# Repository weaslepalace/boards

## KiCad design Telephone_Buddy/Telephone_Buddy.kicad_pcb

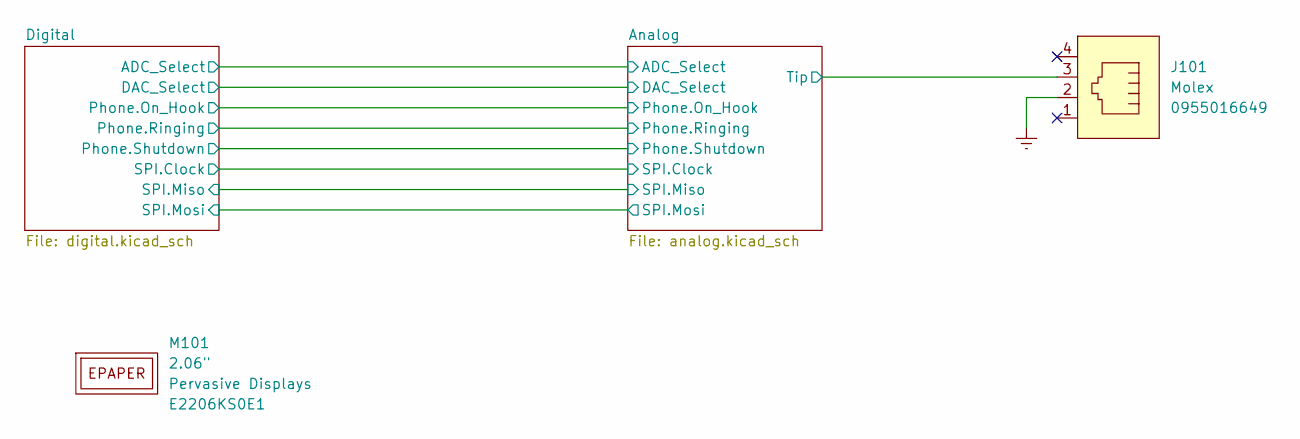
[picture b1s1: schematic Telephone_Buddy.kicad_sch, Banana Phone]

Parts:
J101: Molex_RJ11; Manufacturer Part Number 0955016649
M101: 2.06"; Pervasive_E2206KS0E1; Manufacturer Part Number E2206KS0E1

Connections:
/Analog/Tip: J101.3; also elsewhere on the board
GND: J101.2; also elsewhere on the board

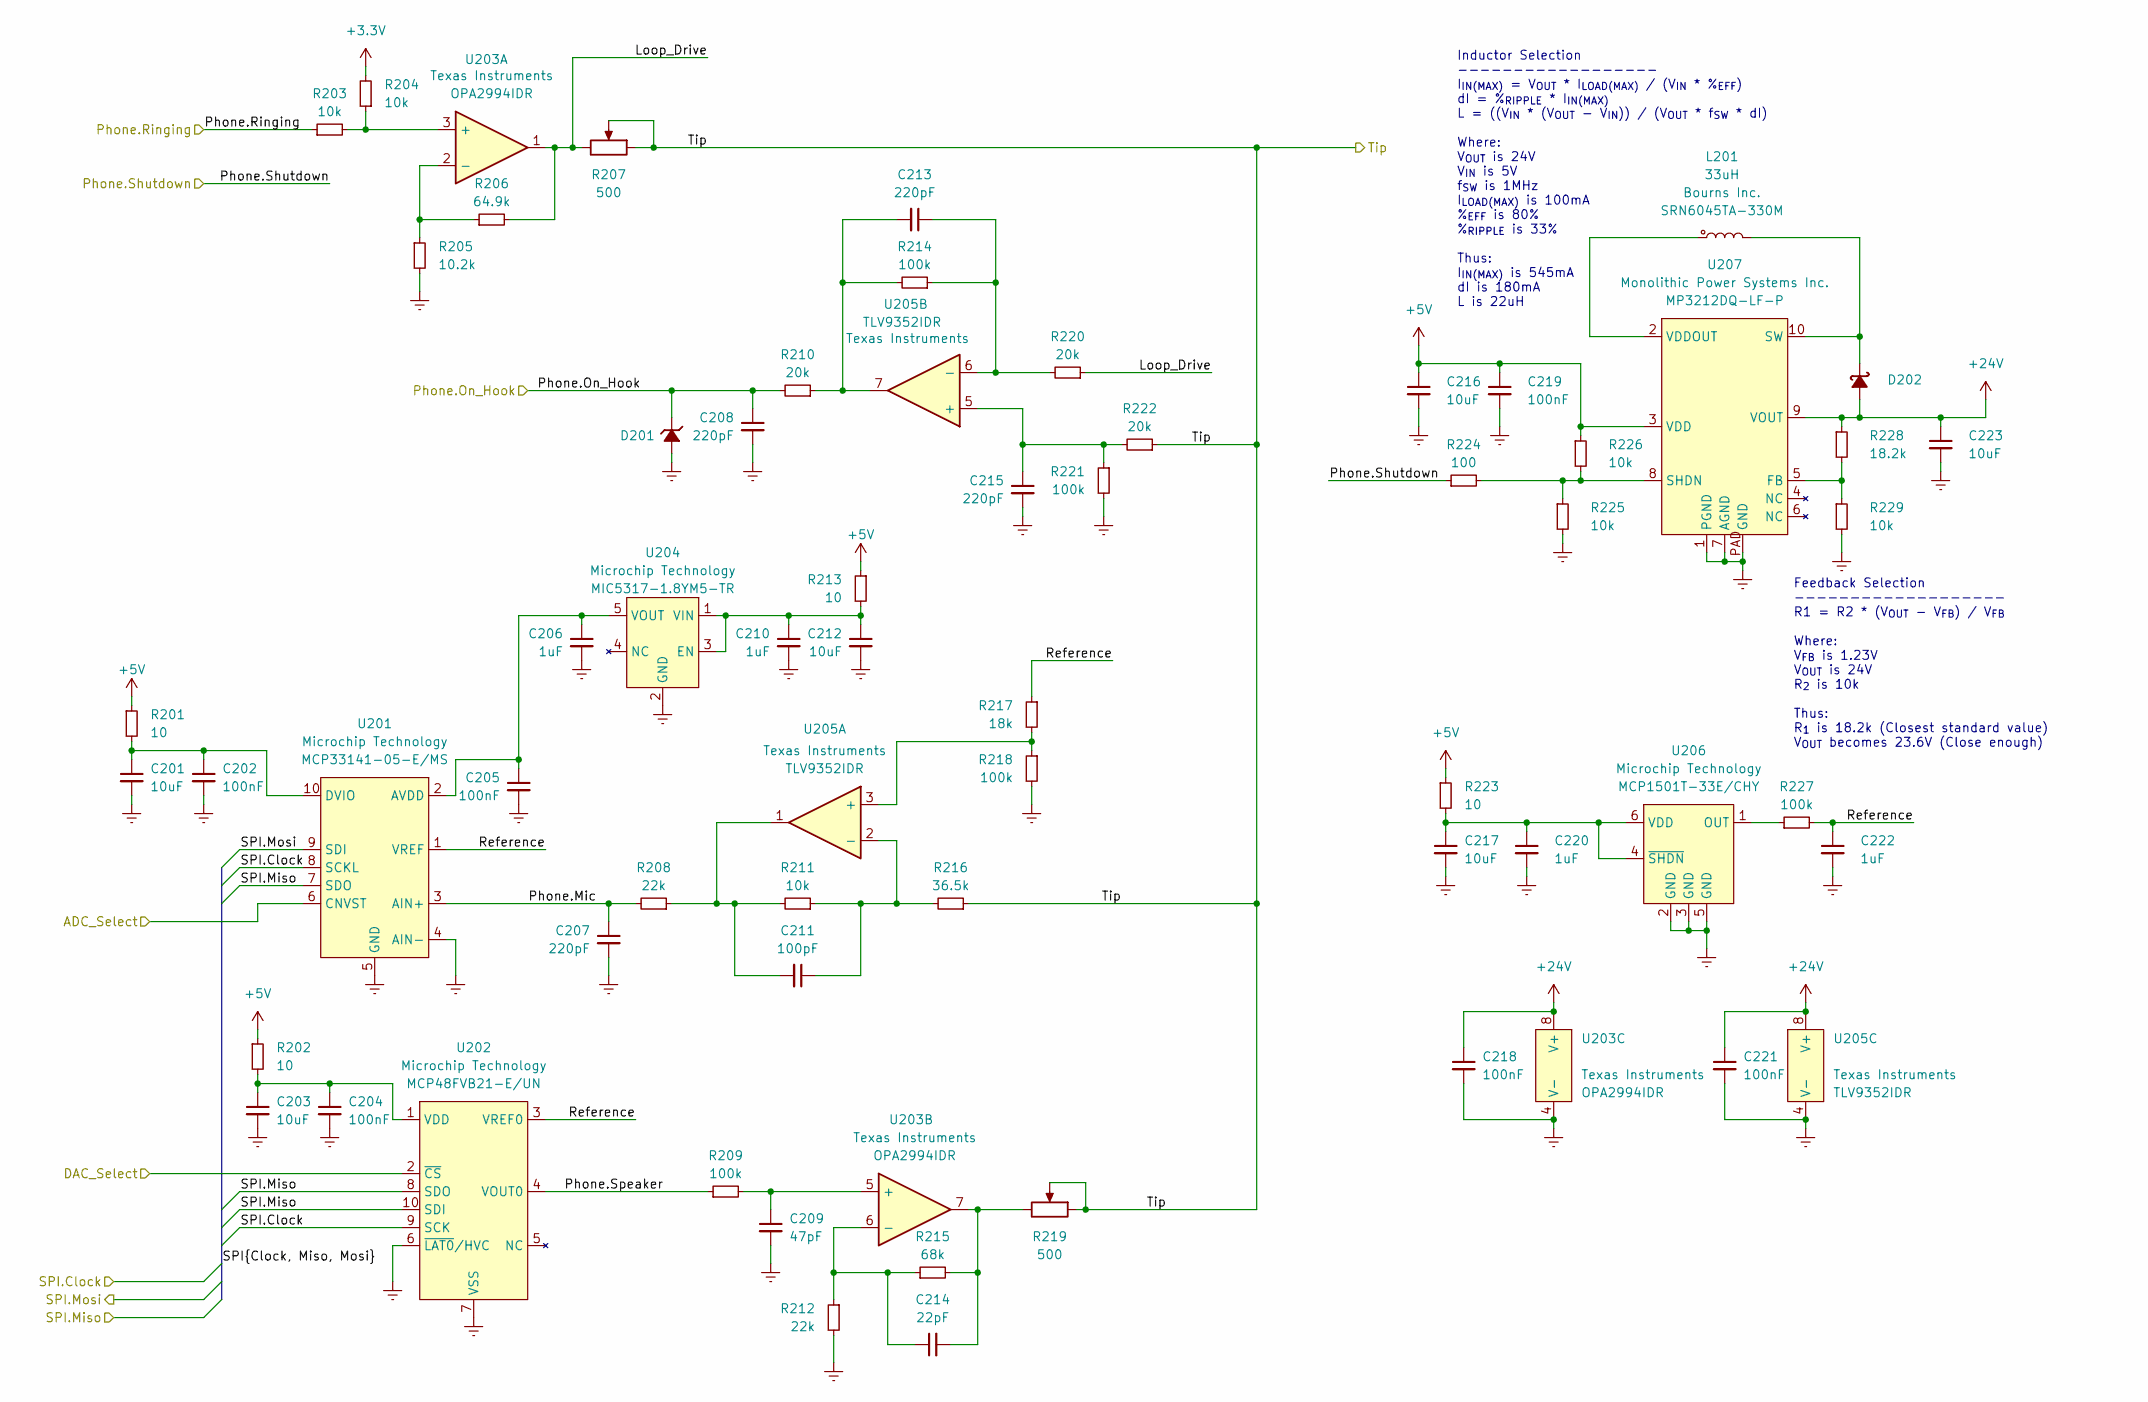
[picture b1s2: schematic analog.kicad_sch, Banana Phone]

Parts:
C201, C203, C212, C217: 10uF; C_0603; Manufacturer Part Number GRM188R61A106ME69D
C202, C204, C205, C218, C219, C221: 100nF; C_0603; Manufacturer Part Number GCJ188R72A104KA01D
C206, C210, C220, C222: 1uF; C_0603; Manufacturer Part Number GCJ188R71E105KA01D
C207, C208, C213, C215: 220pF; C_0603; Manufacturer Part Number GCM1885C2A221JA16D
C209: 47pF; C_0603; Manufacturer Part Number GCM1885C2A470JA16J
C211: 100pF; C_0603; Manufacturer Part Number GCM1885C2A101JA16D
C214: 22pF; C_0603; Manufacturer Part Number GCM1885C2A220JA16D
C216: 10uF; C_1206; Manufacturer Part Number CL31B106KAHNFNE
C223: 10uF; C_1206; Manufacturer Part Number CL31B106KBHNNNE
D201: onsemi_SOD123; Manufacturer Part Number MMSZ3V3T1G
D202: SOD-123FL; Manufacturer Part Number SS2040FL-AU_R1_000A1
L201: 33uH; Bourns_Inductor-6mmx6mm; Manufacturer Part Number SRN6045TA-330M
R201, R202, R213, R223: 10; R_0603; Manufacturer Part Number RC0603FR-0710RL
R203, R204, R211, R225, R226, R229: 10k; R_0603; Manufacturer Part Number RC0603FR-0710KL
R205: 10.2k; R_0603; Manufacturer Part Number RC0603FR-0710K2L
R206: 64.9k; R_0603; Manufacturer Part Number RC0603FR-0764K9L
R207, R219: 500; Bourns_SMD3-J-Lead-4.5mm; Manufacturer Part Number 3314J-1-501G
R208, R212: 22k; R_0603; Manufacturer Part Number RC0603FR-0722KL
R209, R214, R218, R221, R227: 100k; R_0603; Manufacturer Part Number RC0603FR-07100KL
R210, R220, R222: 20k; R_0603; Manufacturer Part Number RC0603FR-0720KL
R215: 68k; R_0603; Manufacturer Part Number RC0603FR-0768KL
R216: 36.5k; R_0603; Manufacturer Part Number RC0603FR-0736K5L
R217: 18k; R_0603; Manufacturer Part Number RC0603FR-0718KL
R224: 100; R_0603; Manufacturer Part Number RC0603FR-07100RL
R228: 18.2k; R_0603; Manufacturer Part Number RC0603FR-0718K2L
U201: Microchip_MSOP-10; Manufacturer Part Number MCP33141-05-E/MS
U202: Microchip_MSOP-10; Manufacturer Part Number MCP48FVB21-E/UN
U203: Microchip_SOIC_8; Manufacturer Part Number OPA2994IDR
U204: TI_SOT_23_5; Manufacturer Part Number MIC5317-1.8YM5-TR
U205: TI_SOIC-8; Manufacturer Part Number TLV9352IDR
U206: Microchip_SOT23-6; Manufacturer Part Number MCP1501T-33E/CHY
U207: Monolithic_DFN-10; Manufacturer Part Number MP3212DQ-LF-P

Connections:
+3.3V: R204.2; also elsewhere on the board
+24V: C218.1, C221.1, C223.1, D202.2 (A), R228.1, U203.8 (V+), U205.8 (V+), U207.9 (VOUT)
/Analog/ADC_Select: U201.6 (CNVST); also elsewhere on the board
/Analog/DAC_Select: U202.2 (~CS); also elsewhere on the board
/Analog/Loop_Drive: R206.2, R207.3, R220.1, U203.1
/Analog/Phone.Mic: C207.1, R208.2, U201.3 (AIN+)
/Analog/Phone.On_Hook: C208.1, D201.1 (K), R210.2; also elsewhere on the board
/Analog/Phone.Ringing: R203.1; also elsewhere on the board
/Analog/Phone.Shutdown: R224.1; also elsewhere on the board
/Analog/Phone.Speaker: R209.1, U202.4 (VOUT0)
/Analog/Reference: C222.1, R217.1, R227.2, U201.1 (VREF), U202.3 (VREF0)
/Analog/SPI.Clock: U201.8 (SCKL), U202.9 (SCK); also elsewhere on the board
/Analog/SPI.Miso: U201.7 (SDO), U202.8 (SDO), U202.10 (SDI); also elsewhere on the board
/Analog/SPI.Mosi: U201.9 (SDI); also elsewhere on the board
/Analog/Tip: R207.1, R207.2, R216.1, R219.1, R219.2, R222.1; also elsewhere on the board
GND: C201.2, C202.2, C203.2, C204.2, C205.2, C206.2, C207.2, C208.2, C209.2, C210.2, C212.2, C215.2, C216.2, C217.2, C218.2, C219.2, C220.2, C221.2, C222.2, C223.2, D201.2 (A), R205.2, R212.2, R218.2, R221.2, R225.2, R229.2, U201.4 (AIN-), U201.5 (GND), U202.6 (~LAT0/HVC), U202.7 (VSS), U203.4 (V-), U204.2 (GND), U205.4 (V-), U206.2 (GND), U206.3 (GND), U206.5 (GND), U207.1 (PGND), U207.7 (AGND), U207.PAD (GND); also elsewhere on the board
unnamed: C211.2, R208.1, R211.2, U205.1
unnamed: C213.2, R210.1, R214.2, U205.7
unnamed: C214.2, R215.2, R219.3, U203.7
unnamed: D202.1 (K), L201.2, U207.10 (SW)
unnamed: C205.1, C206.1, U201.2 (AVDD), U204.5 (VOUT)
unnamed: C201.1, C202.1, R201.2, U201.10 (DVIO)
unnamed: C203.1, C204.1, R202.2, U202.1 (VDD)
unnamed: R203.2, R204.1, U203.3 (+)
unnamed: R205.1, R206.1, U203.2 (-)
unnamed: C209.1, R209.2, U203.5 (+)
unnamed: C214.1, R212.1, R215.1, U203.6 (-)
unnamed: C210.1, C212.1, R213.2, U204.1 (VIN), U204.3 (EN)
unnamed: R217.2, R218.1, U205.3 (+)
unnamed: C211.1, R211.1, R216.2, U205.2 (-)
unnamed: C215.1, R221.1, R222.2, U205.5 (+)
unnamed: C213.1, R214.1, R220.2, U205.6 (-)
unnamed: R227.1, U206.1 (OUT)
unnamed: C217.1, C220.1, R223.2, U206.4 (~SHDN), U206.6 (VDD)
unnamed: R228.2, R229.1, U207.5 (FB)
unnamed: R224.2, R225.1, R226.2, U207.8 (SHDN)
unnamed: L201.1, U207.2 (VDDOUT)
V_+5V: C216.1, C219.1, R201.1, R202.1, R213.1, R223.1, R226.1, U207.3 (VDD); also elsewhere on the board

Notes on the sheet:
Inductor Selection ------------------ I_{IN(MAX)} = V_{OUT} * I_{LOAD(MAX)} / (V_{IN} * %_{EFF}) dI = %_{RIPPLE} * I_{IN(MAX)} L = ((V_{IN} * (V_{OUT} - V_{IN})) / (V_{OUT} * f_{SW} * dI) Where: V_{OUT} is 24V V_{IN} is 5V f_{SW} is 1MHz I_{LOAD(MAX)} is 100mA %_{EFF} is 80% %_{RIPPLE} is 33% Thus: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
Feedback Selection ------------------- R1 = R2 * (V_{OUT} - V_{FB}) / V_{FB} Where: V_{FB} is 1.23V V_{OUT} is 24V R_{2} is 10k Thus: R_{1} is 18.2k (Closest standard value) V_{OUT} becomes 23.6V (Close enough)

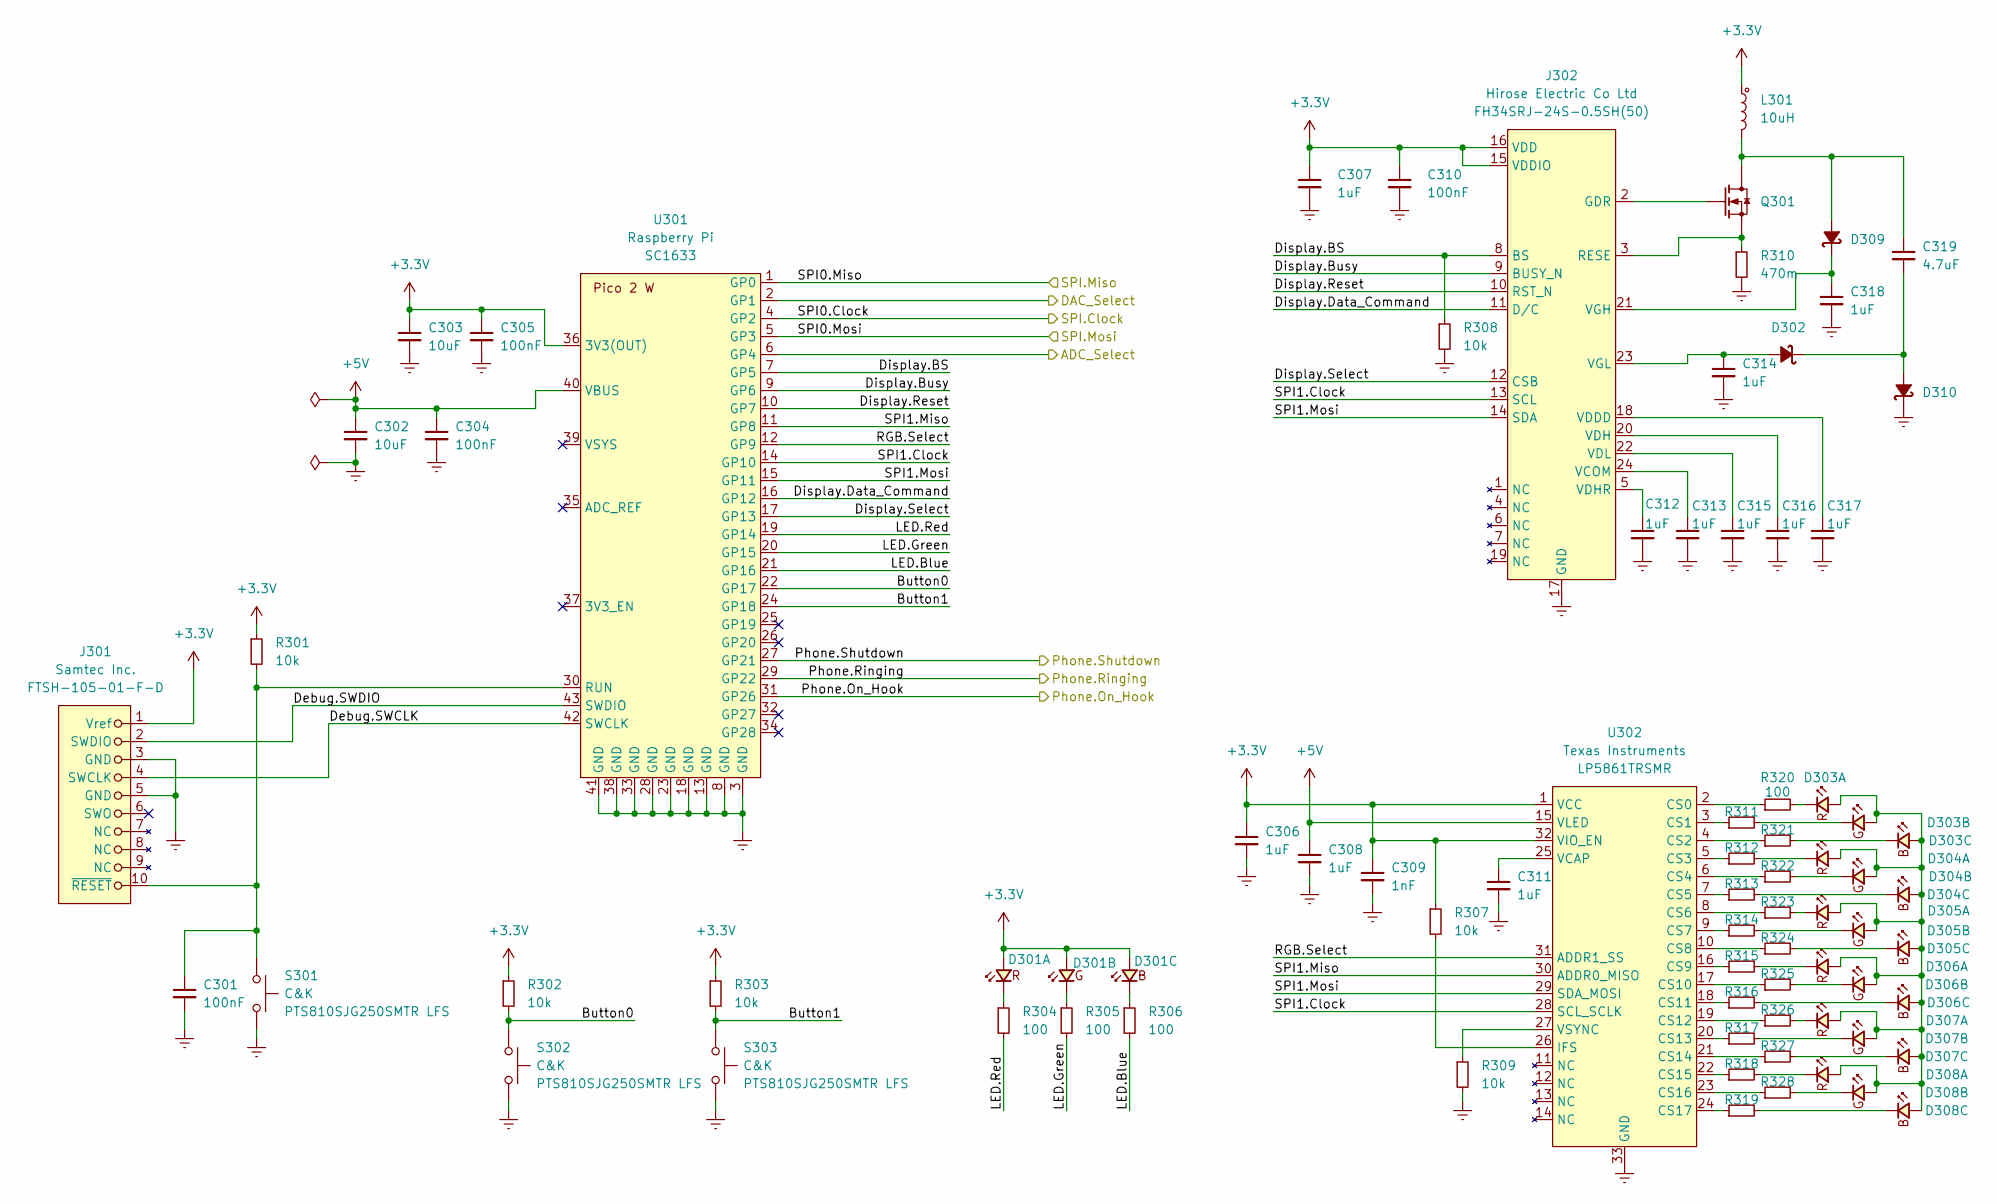
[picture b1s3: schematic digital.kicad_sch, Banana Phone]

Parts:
C301, C304, C305, C310: 100nF; C_0603; Manufacturer Part Number GCJ188R72A104KA01D
C302, C303: 10uF; C_0603; Manufacturer Part Number GRM188R61A106ME69D
C306, C307, C308, C311, C312, C313, C314, C315, C316, C317, C318: 1uF; C_0603; Manufacturer Part Number GCJ188R71E105KA01D
C309: 1nF; C_0603; Manufacturer Part Number GRM1885C1H102JA01D
C319: 4.7uF; C_0805; Manufacturer Part Number CL21B475KOFNFNE
D301, D303, D304, D305, D306, D307, D308: Everlight_0606-4SMD; Manufacturer Part Number EAST1616RGBB2
D302, D309, D310: SOD-123FL; Manufacturer Part Number SS2040FL-AU_R1_000A1
J301: Samtec_FTSH_10pin_Unshrouded; Manufacturer Part Number FTSH-105-01-F-D
J302: Hirose_ZIF-24-0.5mm; Manufacturer Part Number FH34SRJ-24S-0.5SH(50)
L301: 10uH; Abracon_ASPI-4030S; Manufacturer Part Number ASPI-4030S-100M-T
Q301: Diodes_SOT323-3-MOSFET; Manufacturer Part Number DMN3065LW-7
R301, R302, R303, R307, R308, R309: 10k; R_0603; Manufacturer Part Number RC0603FR-0710KL
R304, R305, R306, R311, R312, R313, R314, R315, R316, R317, R318, R319, R320, R321, R322, R323, R324, R325, R326, R327, R328: 100; R_0603; Manufacturer Part Number RC0603FR-07100RL
R310: 470m; R_0603; Manufacturer Part Number RL0603FR-070R47L
S301, S302, S303: CK_PTS810; Manufacturer Part Number PTS810SJG250SMTR LFS
U301: RaspberryPi_Pico-2-W; Manufacturer Part Number SC1633
U302: TI_VQFN32; Manufacturer Part Number LP5861TRSMR

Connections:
+3.3V: C303.1, C305.1, C306.1, C307.1, C309.1, C310.1, D301.4 (A), J301.1 (Vref), J302.15 (VDDIO), J302.16 (VDD), L301.1, R301.1, R302.1, R303.1, R307.1, U301.36 (3V3(OUT)), U302.1 (VCC), U302.32 (VIO_EN); also elsewhere on the board
/Analog/ADC_Select: U301.6 (GP4); also elsewhere on the board
/Analog/DAC_Select: U301.2 (GP1); also elsewhere on the board
/Analog/Phone.On_Hook: U301.31 (GP26); also elsewhere on the board
/Analog/Phone.Ringing: U301.29 (GP22); also elsewhere on the board
/Analog/Phone.Shutdown: U301.27 (GP21); also elsewhere on the board
/Analog/SPI.Clock: U301.4 (GP2); also elsewhere on the board
/Analog/SPI.Miso: U301.1 (GP0); also elsewhere on the board
/Analog/SPI.Mosi: U301.5 (GP3); also elsewhere on the board
/Digital/Button0: R302.2, S302.1, U301.22 (GP17)
/Digital/Button1: R303.2, S303.1, U301.24 (GP18)
/Digital/Debug.SWCLK: J301.4 (SWCLK), U301.42 (SWCLK)
/Digital/Debug.SWDIO: J301.2 (SWDIO), U301.43 (SWDIO)
/Digital/Display.BS: J302.8 (BS), R308.1, U301.7 (GP5)
/Digital/Display.Busy: J302.9 (BUSY_N), U301.9 (GP6)
/Digital/Display.Data_Command: J302.11 (D/C), U301.16 (GP12)
/Digital/Display.Reset: J302.10 (RST_N), U301.10 (GP7)
/Digital/Display.Select: J302.12 (CSB), U301.17 (GP13)
/Digital/LED.Blue: R306.2, U301.21 (GP16)
/Digital/LED.Green: R305.2, U301.20 (GP15)
/Digital/LED.Red: R304.2, U301.19 (GP14)
/Digital/RGB.Select: U301.12 (GP9), U302.31 (ADDR1_SS)
/Digital/SPI1.Clock: J302.13 (SCL), U301.14 (GP10), U302.28 (SCL_SCLK)
/Digital/SPI1.Miso: U301.11 (GP8), U302.30 (ADDR0_MISO)
/Digital/SPI1.Mosi: J302.14 (SDA), U301.15 (GP11), U302.29 (SDA_MOSI)
GND: C301.2, C302.2, C303.2, C304.2, C305.2, C306.2, C307.2, C308.2, C309.2, C310.2, C311.2, C312.2, C313.2, C314.2, C315.2, C316.2, C317.2, C318.2, D310.1 (K), J301.3 (GND), J301.5 (GND), J302.17 (GND), R308.2, R309.2, R310.2, S301.2, S302.2, S303.2, U301.3 (GND), U301.8 (GND), U301.13 (GND), U301.18 (GND), U301.23 (GND), U301.28 (GND), U301.33 (GND), U301.38 (GND), U301.41 (GND), U302.33 (GND); also elsewhere on the board
unnamed: D301.1 (K), R304.1
unnamed: D301.2 (K), R305.1
unnamed: D301.3 (K), R306.1
unnamed: C314.1, D302.2 (A), J302.23 (VGL)
unnamed: C319.2, D302.1 (K), D310.2 (A)
unnamed: D303.4 (A), D304.4 (A), D305.4 (A), D306.4 (A), D307.4 (A), D308.4 (A)
unnamed: D303.1 (K), R320.2
unnamed: D303.2 (K), R311.2
unnamed: D303.3 (K), R321.2
unnamed: D304.1 (K), R312.2
unnamed: D304.2 (K), R322.2
unnamed: D304.3 (K), R313.2
unnamed: D305.1 (K), R323.2
unnamed: D305.2 (K), R314.2
unnamed: D305.3 (K), R324.2
unnamed: D306.1 (K), R315.2
unnamed: D306.2 (K), R325.2
unnamed: D306.3 (K), R316.2
unnamed: D307.1 (K), R326.2
unnamed: D307.2 (K), R317.2
unnamed: D307.3 (K), R327.2
unnamed: D308.1 (K), R318.2
unnamed: D308.2 (K), R328.2
unnamed: D308.3 (K), R319.2
unnamed: C319.1, D309.2 (A), L301.2, Q301.D
unnamed: C318.1, D309.1 (K), J302.21 (VGH)
unnamed: C301.1, J301.10 (~RESET), R301.2, S301.1, U301.30 (RUN)
unnamed: J302.2 (GDR), Q301.G
unnamed: J302.3 (RESE), Q301.S, R310.1
unnamed: C313.1, J302.24 (VCOM)
unnamed: C317.1, J302.18 (VDDD)
unnamed: C316.1, J302.20 (VDH)
unnamed: C312.1, J302.5 (VDHR)
unnamed: C315.1, J302.22 (VDL)
unnamed: R320.1, U302.2 (CS0)
unnamed: R311.1, U302.3 (CS1)
unnamed: R321.1, U302.4 (CS2)
unnamed: R312.1, U302.5 (CS3)
unnamed: R322.1, U302.6 (CS4)
unnamed: R313.1, U302.7 (CS5)
unnamed: R323.1, U302.8 (CS6)
unnamed: R314.1, U302.9 (CS7)
unnamed: R324.1, U302.10 (CS8)
unnamed: R315.1, U302.16 (CS9)
unnamed: R325.1, U302.17 (CS10)
unnamed: R316.1, U302.18 (CS11)
unnamed: R326.1, U302.19 (CS12)
unnamed: R317.1, U302.20 (CS13)
unnamed: R327.1, U302.21 (CS14)
unnamed: R318.1, U302.22 (CS15)
unnamed: R328.1, U302.23 (CS16)
unnamed: R319.1, U302.24 (CS17)
unnamed: R307.2, U302.26 (IFS)
unnamed: C311.1, U302.25 (VCAP)
unnamed: R309.1, U302.27 (VSYNC)
V_+5V: C302.1, C304.1, C308.1, U301.40 (VBUS), U302.15 (VLED); also elsewhere on the board

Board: 2 copper layers, 130 parts (1 on the bottom side), 109 nets, no tracks yet.

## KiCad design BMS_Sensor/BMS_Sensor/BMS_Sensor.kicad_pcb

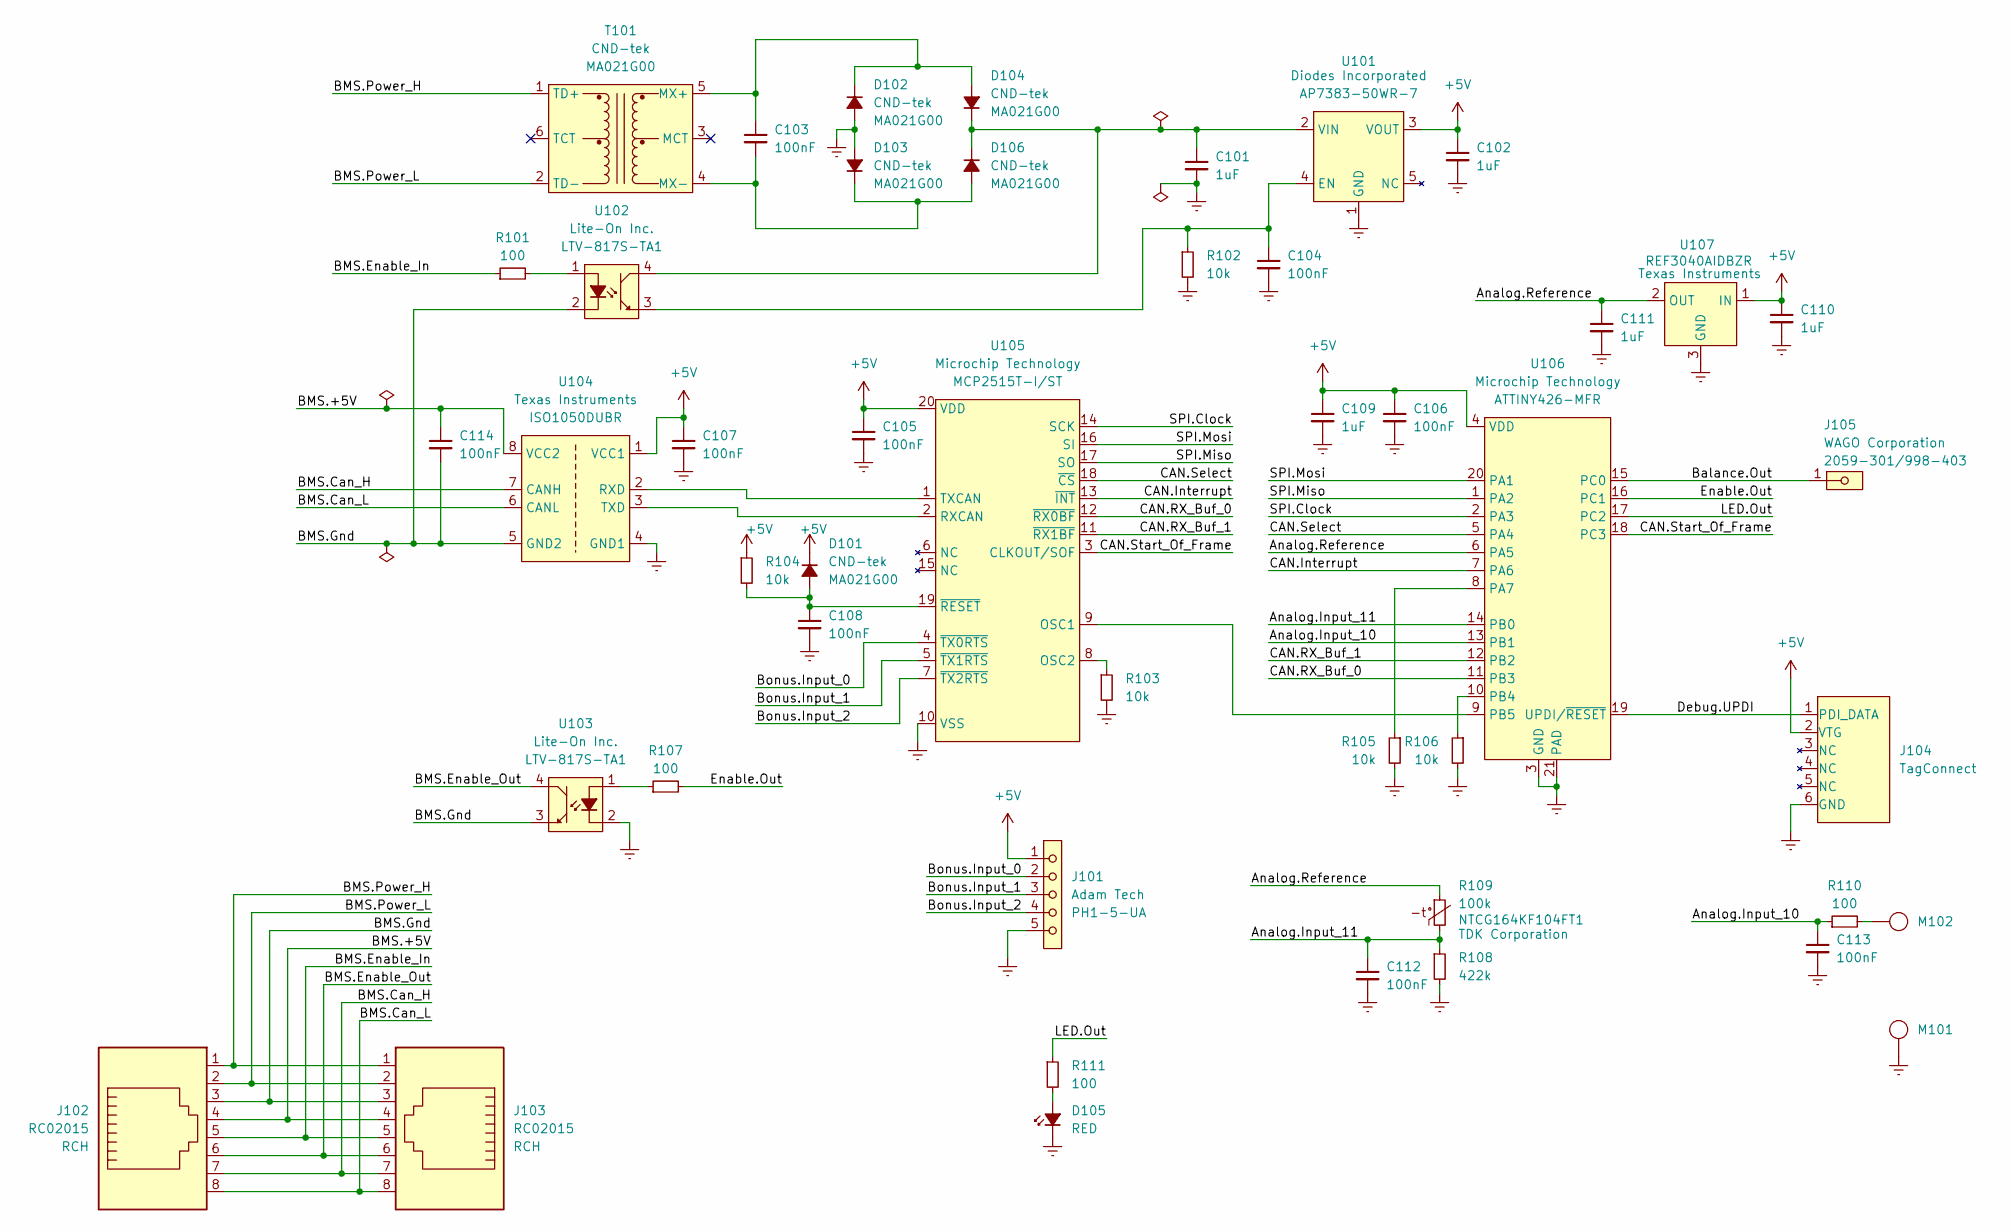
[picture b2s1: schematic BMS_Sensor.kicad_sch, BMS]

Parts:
C101, C102, C109, C110, C111: 1uF; C_0603; Manufacturer Part Number GCJ188R71E105KA01D
C103, C104, C105, C106, C107, C108, C112, C113, C114: 100nF; C_0603; Manufacturer Part Number GCJ188R72A104KA01D
D101, D102, D103, D104, D106: SOD-123FL; Manufacturer Part Number MA021G00
D105: RED; LiteOn_LED0805; Manufacturer Part Number NCD0805R1
J101: Header_1x5; Manufacturer Part Number PH1-5-UA
J102, J103: RCH_RC02015; Manufacturer Part Number RC02015
J104: Tag-Connect_6Pin-No-Legs; Manufacturer Part Number TC2030-PKT-ICESPI-NL
J105: 2059-301_998-403; Manufacturer Part Number 2059-301/998-403
M101, M102: M_M3_Lug_Plated
R101, R107, R110, R111: 100; R_0603; Manufacturer Part Number RC0603FR-07100RL
R102, R103, R104, R105, R106: 10k; R_0603; Manufacturer Part Number RC0603FR-0710KL
R108: 422k; R_0603; Manufacturer Part Number RC0603FR-07422KL
R109: 100k; C_0603; Manufacturer Part Number NTCG164KF104FT1
T101: T_MA21G00; Manufacturer Part Number MA021G00
U101: Diodes_SOT25; Manufacturer Part Number AP7383-50WR-7
U102, U103: LiteOn_LTV817S_SMD4; Manufacturer Part Number LTV-817S-TA1
U104: TI_SOP8-DUB; Manufacturer Part Number ISO1050DUBR
U105: Microchip_TSSOP20; Manufacturer Part Number MCP2515T-I/ST
U106: Microchip_VQFN20; Manufacturer Part Number ATTINY426-MFR
U107: TI_SOT_23_3; Manufacturer Part Number REF3040AIDBZR

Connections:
/Analog.Input_10: C113.1, R110.1, U106.13 (PB1)
/Analog.Input_11: C112.1, R108.1, R109.2, U106.14 (PB0)
/Analog.Reference: C111.1, R109.1, U106.6 (PA5), U107.2 (OUT)
/BMS.+5V: C114.1, J102.4, J103.4, U104.8 (VCC2)
/BMS.Can_H: J102.7, J103.7, U104.7 (CANH)
/BMS.Can_L: J102.8, J103.8, U104.6 (CANL)
/BMS.Enable_In: J102.5, J103.5, R101.1
/BMS.Enable_Out: J102.6, J103.6, U103.4 (C)
/BMS.Gnd: C114.2, J102.3, J103.3, U102.2 (K), U103.3 (E), U104.5 (GND2)
/BMS.Power_H: J102.1, J103.1, T101.1 (TD+)
/BMS.Power_L: J102.2, J103.2, T101.2 (TD-)
/Balance.Out: J105.1, J105.2, U106.15 (PC0)
/Bonus.Input_0: J101.2, U105.4 (~TX0RTS)
/Bonus.Input_1: J101.3, U105.5 (~TX1RTS)
/Bonus.Input_2: J101.4, U105.7 (~TX2RTS)
/CAN.Interrupt: U105.13 (~INT), U106.7 (PA6)
/CAN.RX_Buf_0: U105.12 (~RX0BF), U106.11 (PB3)
/CAN.RX_Buf_1: U105.11 (~RX1BF), U106.12 (PB2)
/CAN.Select: U105.18 (~CS), U106.5 (PA4)
/CAN.Start_Of_Frame: U105.3 (CLKOUT/SOF), U106.18 (PC3)
/Debug.UPDI: J104.1 (PDI_DATA), U106.19 (UPDI/~RESET)
/Enable.Out: R107.2, U106.16 (PC1)
/LED.Out: R111.1, U106.17 (PC2)
/SPI.Clock: U105.14 (SCK), U106.2 (PA3)
/SPI.Miso: U105.17 (SO), U106.1 (PA2)
/SPI.Mosi: U105.16 (SI), U106.20 (PA1)
GND: C101.2, C102.2, C104.2, C105.2, C106.2, C107.2, C108.2, C109.2, C110.2, C111.2, C112.2, C113.2, D102.2 (A), D103.2 (A), D105.1 (K), J101.5, J104.6 (GND), M101.1, R102.2, R103.2, R105.2, R106.2, R108.2, U101.1 (GND), U103.2 (K), U104.4 (GND1), U105.10 (VSS), U106.3 (GND), U106.21 (PAD), U107.3 (GND)
unnamed: C108.1, D101.2 (A), R104.2, U105.19 (~RESET)
unnamed: C103.1, D102.1 (K), D104.2 (A), T101.5 (MX+)
unnamed: C103.2, D103.1 (K), D106.2 (A), T101.4 (MX-)
unnamed: C101.1, D104.1 (K), D106.1 (K), U101.2 (VIN), U102.4 (C)
unnamed: D105.2 (A), R111.2
unnamed: M102.1, R110.2
unnamed: C104.1, R102.1, U101.4 (EN), U102.3 (E)
unnamed: R101.2, U102.1 (A)
unnamed: R107.1, U103.1 (A)
unnamed: U104.2 (RXD), U105.1 (TXCAN)
unnamed: U104.3 (TXD), U105.2 (RXCAN)
unnamed: U105.9 (OSC1), U106.9 (PB5)
unnamed: R103.1, U105.8 (OSC2)
unnamed: R105.1, U106.8 (PA7)
unnamed: R106.1, U106.10 (PB4)
V_+5V: C102.1, C105.1, C106.1, C107.1, C109.1, C110.1, D101.1 (K), J101.1, J104.2 (VTG), R104.1, U101.3 (VOUT), U104.1 (VCC1), U105.20 (VDD), U106.4 (VDD), U107.1 (IN)

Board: 2 copper layers, 46 parts (0 on the bottom side), 43 nets, no tracks yet.

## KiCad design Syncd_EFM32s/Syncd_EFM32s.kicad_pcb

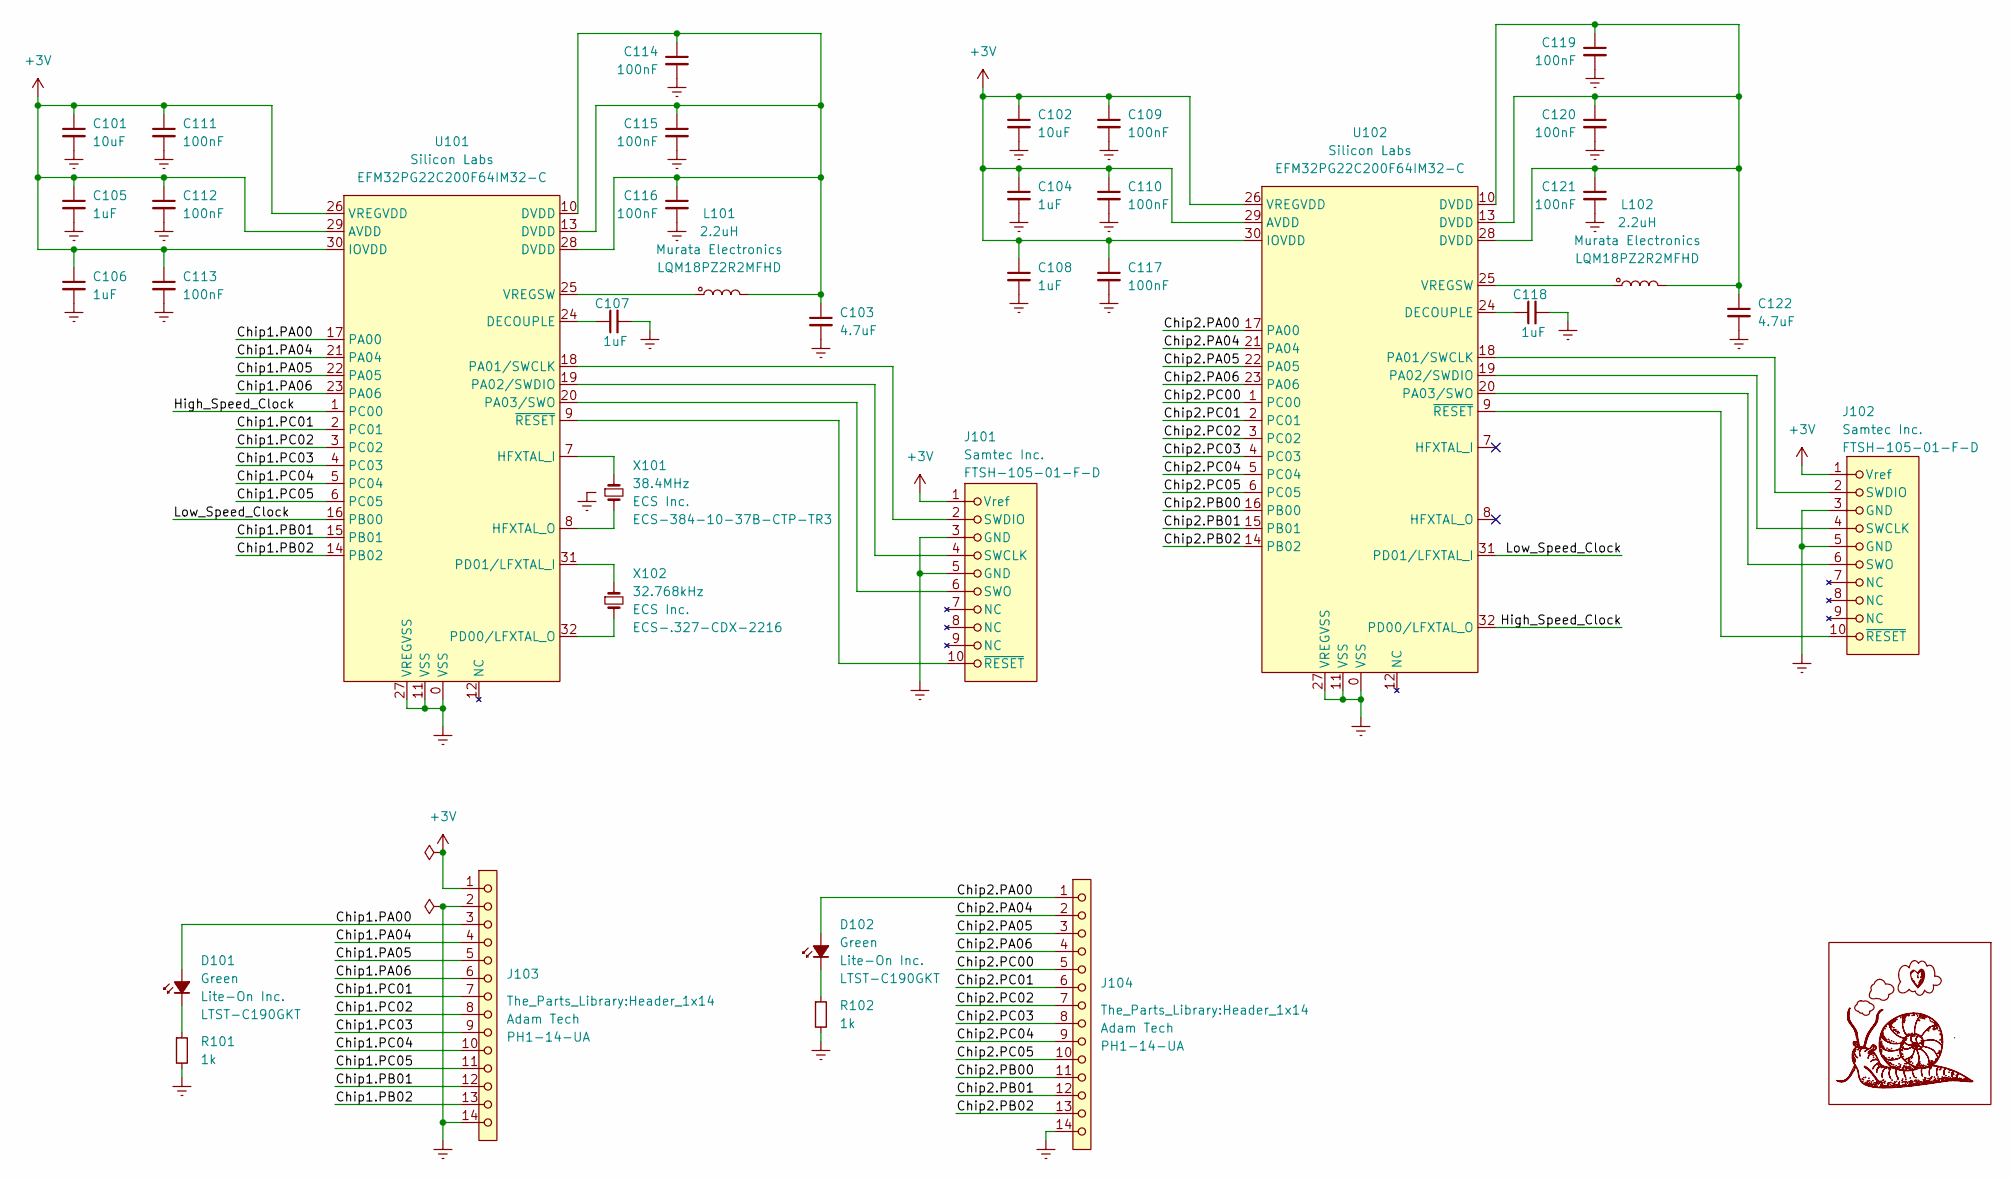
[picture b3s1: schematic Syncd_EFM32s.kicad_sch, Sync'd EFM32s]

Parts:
C101, C102: 10uF; C_1206; Manufacturer Part Number CL31B106KAHNFNE
C103, C122: 4.7uF; C_0805; Manufacturer Part Number CL21B475KOFNFNE
C104, C105, C106, C107, C108, C118: 1uF; C_0603; Manufacturer Part Number GCJ188R71E105KA01D
C109, C110, C111, C112, C113, C114, C115, C116, C117, C119, C120, C121: 100nF; C_0603; Manufacturer Part Number GCJ188R72A104KA01D
D101, D102: Green; LiteOn_LED0603; Manufacturer Part Number LTST-C190GKT
GFX101: Snaily
J101, J102: Samtec_FTSH_10pin_Unshrouded; Manufacturer Part Number FTSH-105-01-F-D
J103, J104: Header_1x14; Manufacturer Part Number PH1-14-UA
L101, L102: 2.2uH; L_0603; Manufacturer Part Number LQM18PZ2R2MFHD
R101, R102: 1k; R_0603; Manufacturer Part Number RC0603FR-071KL
U101, U102: SiLabs_VQFN32; Manufacturer Part Number EFM32PG22C200F64IM32-C
X101: 38.4MHz; ECS_ECX-1637B; Manufacturer Part Number ECS-384-10-37B-CTP-TR3
X102: 32.768kHz; ECS_ECX-16; Manufacturer Part Number ECS-.327-CDX-2216

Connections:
+3V: C101.1, C102.1, C104.1, C105.1, C106.1, C108.1, C109.1, C110.1, C111.1, C112.1, C113.1, C117.1, J101.1 (Vref), J102.1 (Vref), J103.1, U101.26 (VREGVDD), U101.29 (AVDD), U101.30 (IOVDD), U102.26 (VREGVDD), U102.29 (AVDD), U102.30 (IOVDD)
/Chip1.PA00: D101.2 (A), J103.3, U101.17 (PA00)
/Chip1.PA04: J103.4, U101.21 (PA04)
/Chip1.PA05: J103.5, U101.22 (PA05)
/Chip1.PA06: J103.6, U101.23 (PA06)
/Chip1.PB01: J103.12, U101.15 (PB01)
/Chip1.PB02: J103.13, U101.14 (PB02)
/Chip1.PC01: J103.7, U101.2 (PC01)
/Chip1.PC02: J103.8, U101.3 (PC02)
/Chip1.PC03: J103.9, U101.4 (PC03)
/Chip1.PC04: J103.10, U101.5 (PC04)
/Chip1.PC05: J103.11, U101.6 (PC05)
/Chip2.PA00: D102.2 (A), J104.1, U102.17 (PA00)
/Chip2.PA04: J104.2, U102.21 (PA04)
/Chip2.PA05: J104.3, U102.22 (PA05)
/Chip2.PA06: J104.4, U102.23 (PA06)
/Chip2.PB00: J104.11, U102.16 (PB00)
/Chip2.PB01: J104.12, U102.15 (PB01)
/Chip2.PB02: J104.13, U102.14 (PB02)
/Chip2.PC00: J104.5, U102.1 (PC00)
/Chip2.PC01: J104.6, U102.2 (PC01)
/Chip2.PC02: J104.7, U102.3 (PC02)
/Chip2.PC03: J104.8, U102.4 (PC03)
/Chip2.PC04: J104.9, U102.5 (PC04)
/Chip2.PC05: J104.10, U102.6 (PC05)
/High_Speed_Clock: U101.1 (PC00), U102.32 (PD00/LFXTAL_O)
/Low_Speed_Clock: U101.16 (PB00), U102.31 (PD01/LFXTAL_I)
GND: C101.2, C102.2, C103.2, C104.2, C105.2, C106.2, C107.2, C108.2, C109.2, C110.2, C111.2, C112.2, C113.2, C114.2, C115.2, C116.2, C117.2, C118.2, C119.2, C120.2, C121.2, C122.2, J101.3 (GND), J101.5 (GND), J102.3 (GND), J102.5 (GND), J103.2, J103.14, J104.14, R101.2, R102.2, U101.0 (VSS), U101.11 (VSS), U101.27 (VREGVSS), U102.0 (VSS), U102.11 (VSS), U102.27 (VREGVSS), X101.2, X101.4 (GND)
unnamed: C103.1, C114.1, C115.1, C116.1, L101.2, U101.10 (DVDD), U101.13 (DVDD), U101.28 (DVDD)
unnamed: C119.1, C120.1, C121.1, C122.1, L102.2, U102.10 (DVDD), U102.13 (DVDD), U102.28 (DVDD)
unnamed: D101.1 (K), R101.1
unnamed: D102.1 (K), R102.1
unnamed: J101.4 (SWCLK), U101.19 (PA02/SWDIO)
unnamed: J101.2 (SWDIO), U101.18 (PA01/SWCLK)
unnamed: J101.6 (SWO), U101.20 (PA03/SWO)
unnamed: J101.10 (~RESET), U101.9 (~RESET)
unnamed: J102.4 (SWCLK), U102.19 (PA02/SWDIO)
unnamed: J102.2 (SWDIO), U102.18 (PA01/SWCLK)
unnamed: J102.6 (SWO), U102.20 (PA03/SWO)
unnamed: J102.10 (~RESET), U102.9 (~RESET)
unnamed: C107.1, U101.24 (DECOUPLE)
unnamed: U101.7 (HFXTAL_I), X101.3
unnamed: U101.8 (HFXTAL_O), X101.1
unnamed: U101.32 (PD00/LFXTAL_O), X102.2
unnamed: U101.31 (PD01/LFXTAL_I), X102.1
unnamed: L101.1, U101.25 (VREGSW)
unnamed: C118.1, U102.24 (DECOUPLE)
unnamed: L102.1, U102.25 (VREGSW)

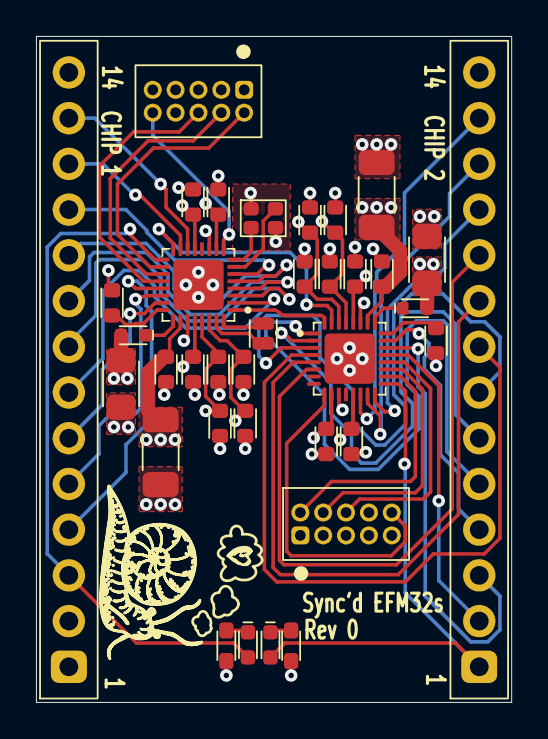
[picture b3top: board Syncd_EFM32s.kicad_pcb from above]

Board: 4 copper layers, 26.4 x 37.0 mm, 37 parts (0 on the bottom side), 48 nets.
